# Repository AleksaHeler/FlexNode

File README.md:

# FlexNode

FlexNode is a DIY "smart home" system with a single hub and multiple flexible and customizable nodes.

## System Diagram

### Node proof of concept

Some images during building:

Grafana screenshots showing it in action:

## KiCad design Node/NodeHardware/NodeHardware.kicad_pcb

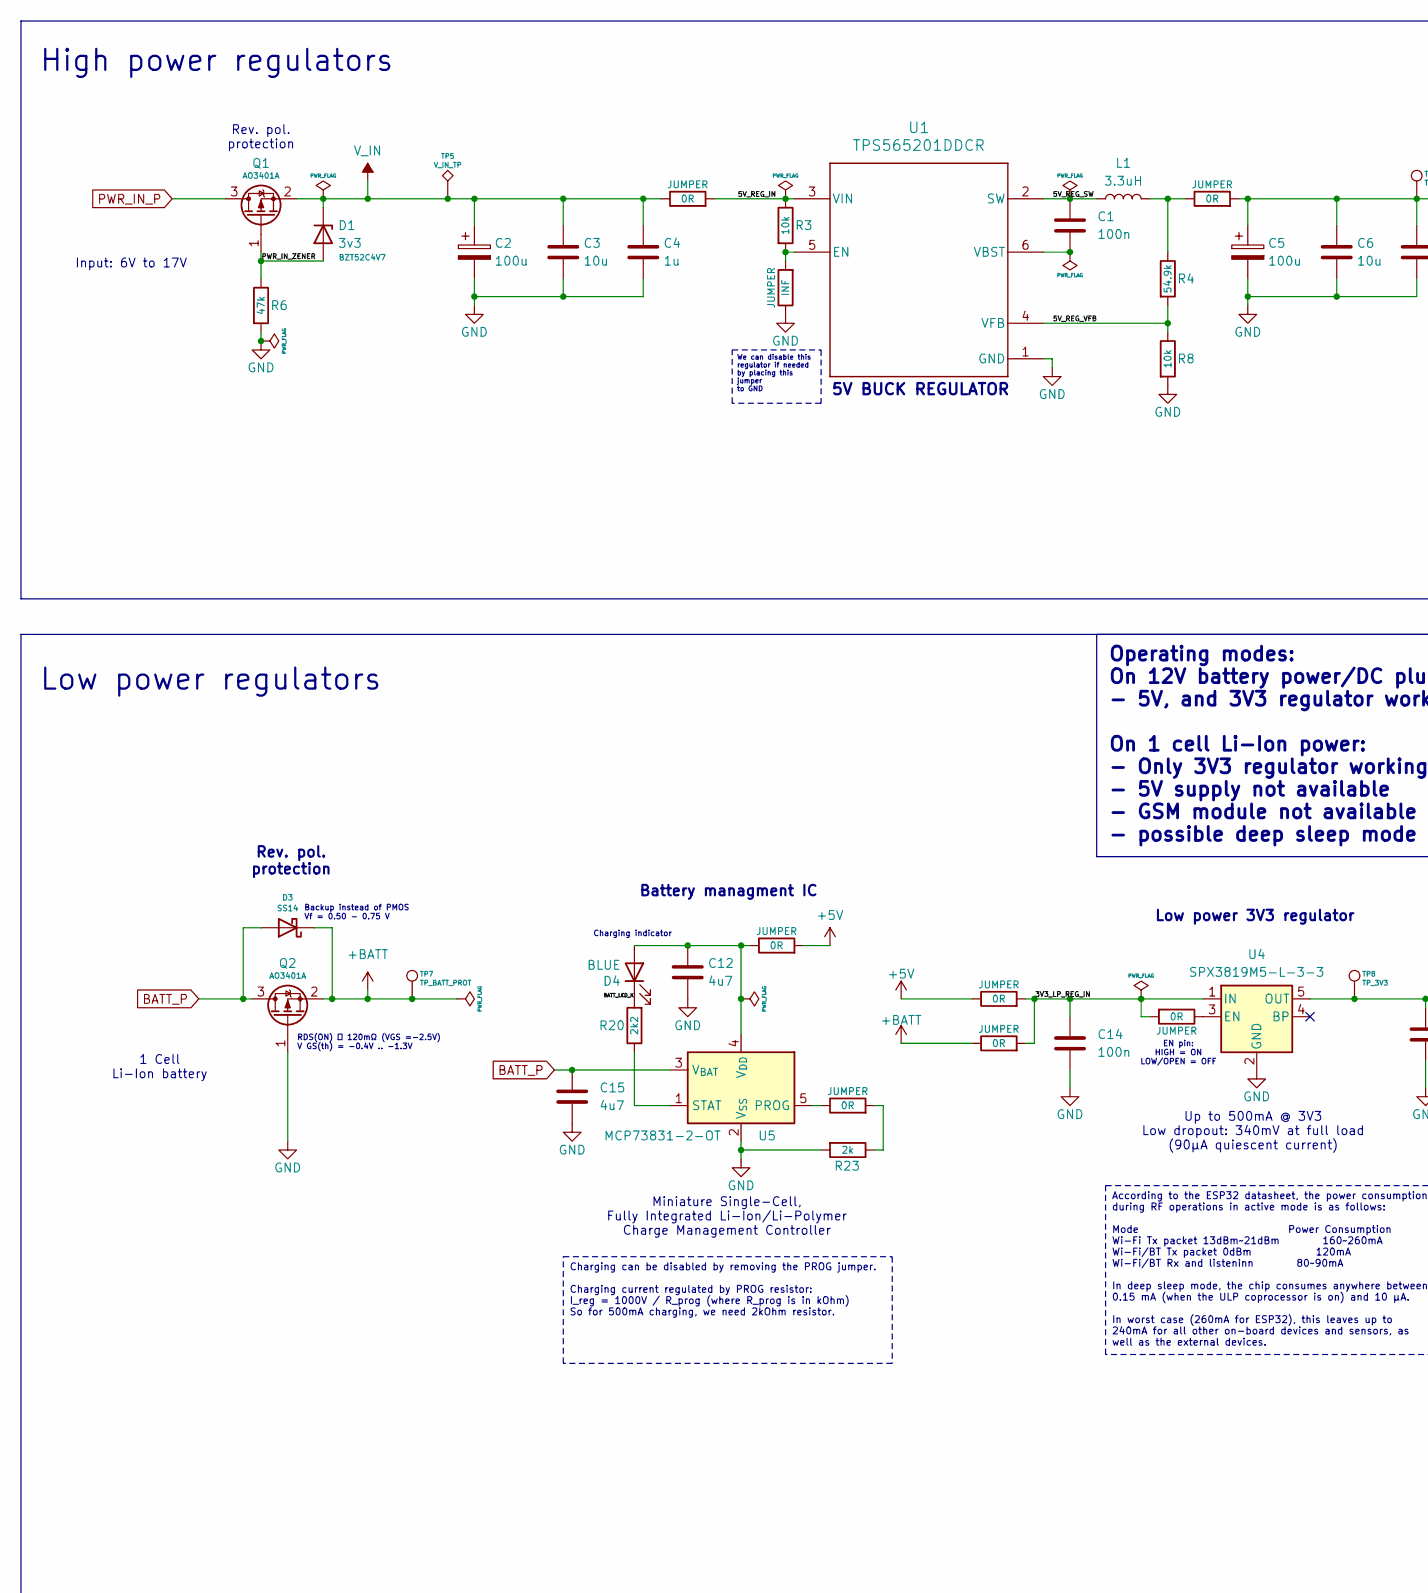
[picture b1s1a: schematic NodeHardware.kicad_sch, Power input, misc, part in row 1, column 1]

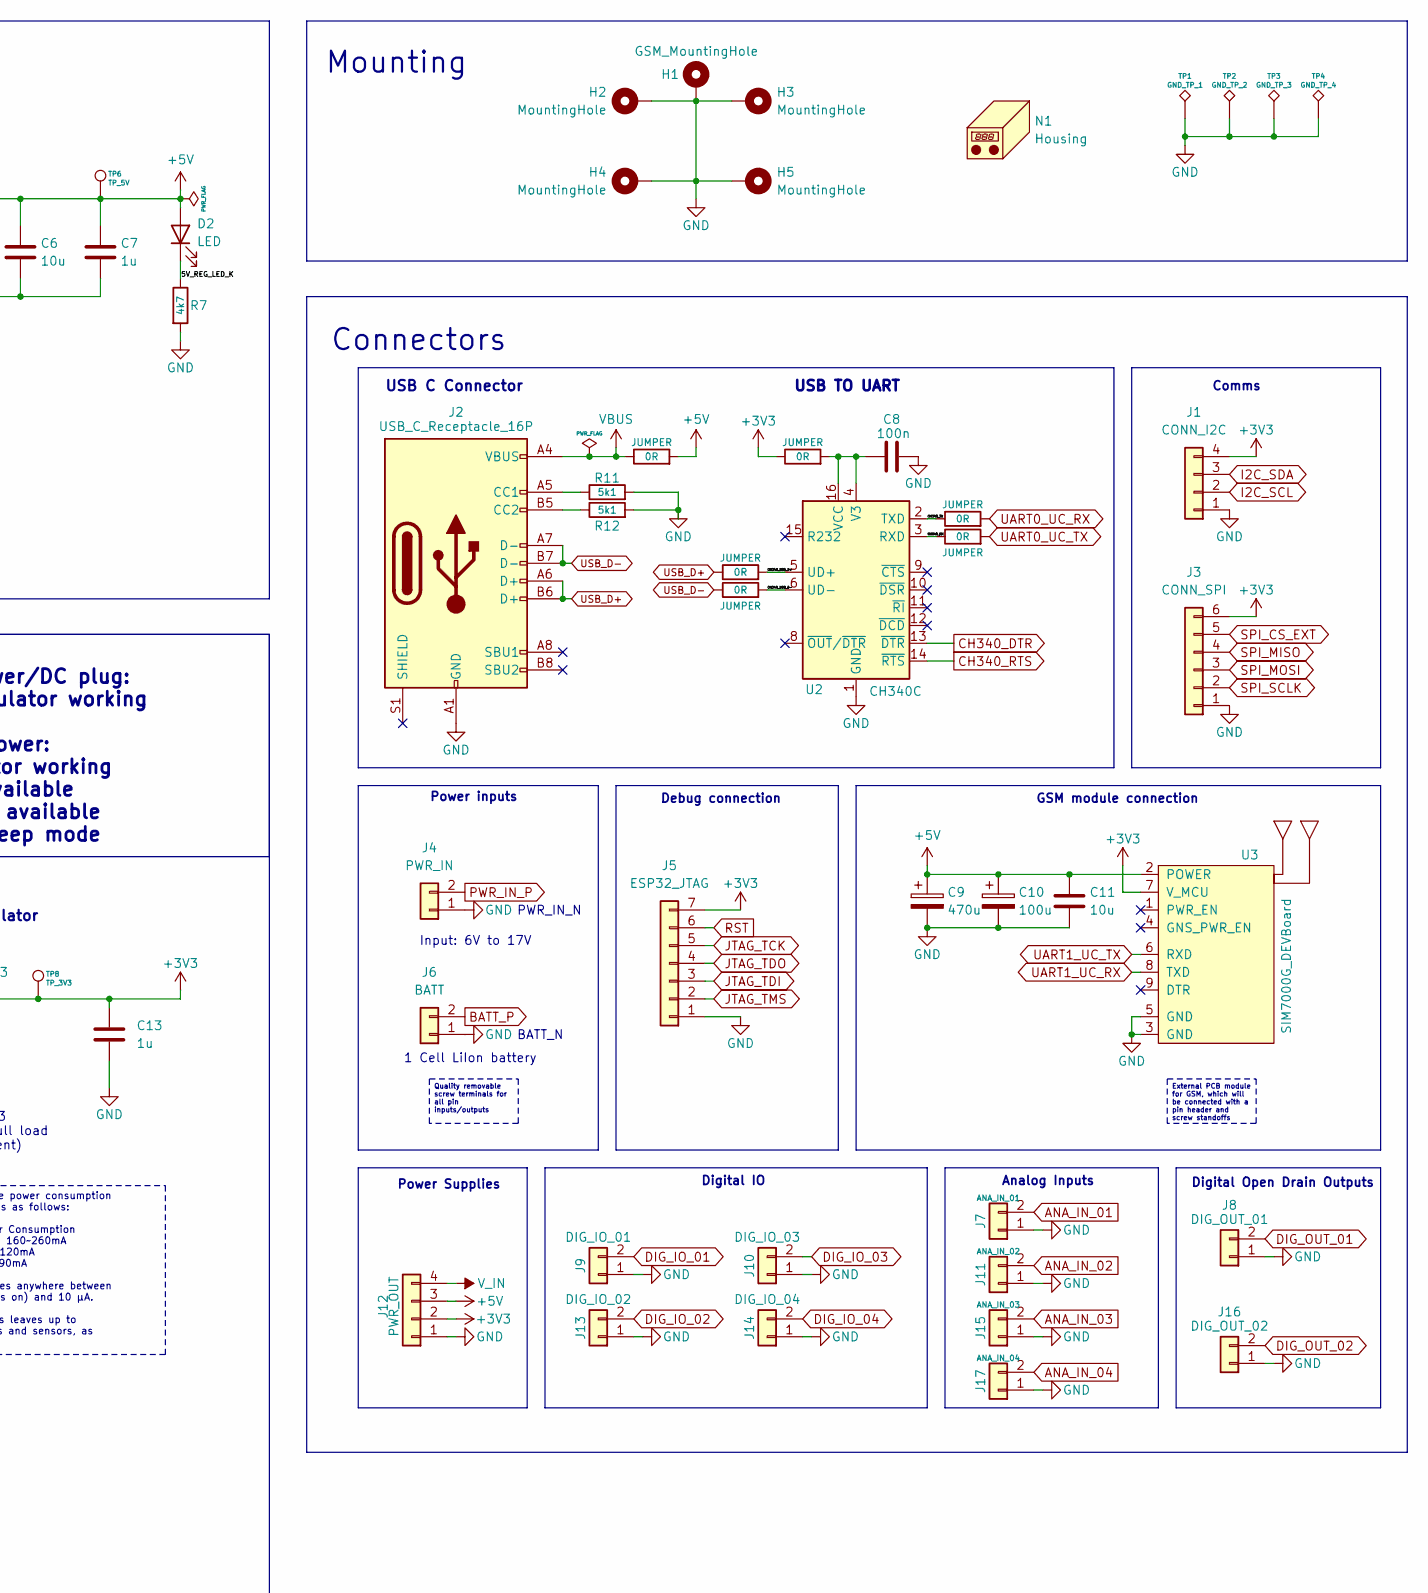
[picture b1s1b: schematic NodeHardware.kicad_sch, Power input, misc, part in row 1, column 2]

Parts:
C1, C8, C14: 100n; C_0805_2012Metric
C2, C5, C10: 100u; CP_Elec_6.3x7.7
C3, C6, C11: 10u; C_0805_2012Metric
C4, C7, C13: 1u; C_0805_2012Metric
C9: 470u; CP_Elec_6.3x7.7
C12, C15: 4u7; C_0805_2012Metric
D1: 3v3; D_SOD-123; Part Name BZT52C4V7
D2: LED; LED_1210_3225Metric
D3: SS14; D_SMA
D4: BLUE; LED_1210_3225Metric
H1: GSM_MountingHole; MountingHole_3.2mm_M3_Pad_Via
H2, H3, H4, H5: MountingHole; MountingHole_3.2mm_M3_Pad_Via
J1: CONN_I2C; TerminalBlock_bornier-4_P5.08mm
J2: USB_C_Receptacle_16P; USB_C_Receptacle_G-Switch_GT-USB-7010ASV
J3: CONN_SPI; TerminalBlock_bornier-6_P5.08mm
J4: PWR_IN; TerminalBlock_bornier-2_P5.08mm
J5: ESP32_JTAG; PinHeader_1x07_P2.54mm_Vertical
J6: BATT; TerminalBlock_bornier-2_P5.08mm
J7: ANA_IN_01; TerminalBlock_bornier-2_P5.08mm
J8: DIG_OUT_01; TerminalBlock_bornier-2_P5.08mm
J9: DIG_IO_01; TerminalBlock_bornier-2_P5.08mm
J10: DIG_IO_03; TerminalBlock_bornier-2_P5.08mm
J11: ANA_IN_02; TerminalBlock_bornier-2_P5.08mm
J12: PWR_OUT; TerminalBlock_bornier-4_P5.08mm
J13: DIG_IO_02; TerminalBlock_bornier-2_P5.08mm
J14: DIG_IO_04; TerminalBlock_bornier-2_P5.08mm
J15: ANA_IN_03; TerminalBlock_bornier-2_P5.08mm
J16: DIG_OUT_02; TerminalBlock_bornier-2_P5.08mm
J17: ANA_IN_04; TerminalBlock_bornier-2_P5.08mm
L1: 3.3uH; L_6.3x6.3_H3
N1: Housing; PlasticEnclosure_150x110x70
Q1, Q2: AO3401A; SOT-23
R1, R2, R9, R10, R13, R14, R15, R16, R17, R18, R19, R21, R22: 0R; R_0805_2012Metric
R3, R8: 10k; R_0805_2012Metric
R4: 54.9k; R_0805_2012Metric
R5: INF; R_0805_2012Metric
R6: 47k; R_0805_2012Metric
R7: 4k7; R_0805_2012Metric
R11, R12: 5k1; R_0805_2012Metric
R20: 2k2; R_0805_2012Metric
R23: 2k; R_0805_2012Metric
TP1: GND_TP_1; TestPoint_Pad_D2.0mm
TP2: GND_TP_2; TestPoint_Pad_D2.0mm
TP3: GND_TP_3; TestPoint_Pad_D2.0mm
TP4: GND_TP_4; TestPoint_Pad_D2.0mm
TP5: V_IN_TP; TestPoint_Pad_D2.0mm
TP6: TP_5V; TestPoint_Pad_D2.0mm
TP7: TP_BATT_PROT; TestPoint_Pad_D2.0mm
TP8: TP_3V3; TestPoint_Pad_D2.0mm
U1: TPS565201DDCR; TPS565201DDCR_L
U2: CH340C; SOIC-16_3.9x9.9mm_P1.27mm
U3: SIM7000G_DEVBoard; sim7000G_dev_board_rev3
U4: SPX3819M5-L-3-3; SOT-23-5
U5: MCP73831-2-OT; SOT-23-5

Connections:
+3V3: C13.1, J1.4, J3.6, J5.7, J12.2, R10.1, TP8.1, U3.7 (V_MCU), U4.5 (OUT); also elsewhere on the board
+5V: C5.1, C6.1, C7.1, C9.1, C10.1, C11.1, D2.2 (A), J12.3, R2.2, R9.2, R17.2, R18.1, TP6.1, U3.2 (POWER); also elsewhere on the board
+BATT: D3.1 (K), Q2.2 (S), R21.1, TP7.1; also elsewhere on the board
/3V3_LP_REG_IN: C14.1, R18.2, R19.2, R21.2, U4.1 (IN)
/5V_REG_IN: R1.2, R3.1, U1.3 (VIN)
/5V_REG_LED_K: D2.1 (K), R7.1
/5V_REG_SW: C1.1, L1.1, U1.2 (SW)
/5V_REG_VFB: R4.2, R8.1, U1.4 (VFB)
/BATT_LED_K: D4.1 (K), R20.2
/CH340_RX: R14.1, U2.3 (RXD)
/CH340_TX: R13.1, U2.2 (TXD)
/CH340_USB_D+: R15.2, U2.5 (UD+)
/CH340_USB_D-: R16.2, U2.6 (UD-)
/PWR_IN_ZENER: D1.2 (A), Q1.1 (G), R6.1
ANA_IN_01: J7.2; also elsewhere on the board
ANA_IN_02: J11.2; also elsewhere on the board
ANA_IN_03: J15.2; also elsewhere on the board
ANA_IN_04: J17.2; also elsewhere on the board
BATT_P: C15.1, D3.2 (A), J6.2, Q2.3 (D), U5.3 (V_{BAT})
CH340_DTR: U2.13 (~DTR); also elsewhere on the board
CH340_RTS: U2.14 (~RTS); also elsewhere on the board
DIG_IO_01: J9.2; also elsewhere on the board
DIG_IO_02: J13.2; also elsewhere on the board
DIG_IO_03: J10.2; also elsewhere on the board
DIG_IO_04: J14.2; also elsewhere on the board
DIG_OUT_01: J8.2; also elsewhere on the board
DIG_OUT_02: J16.2; also elsewhere on the board
GND: C2.2, C3.2, C4.2, C5.2, C6.2, C7.2, C8.2, C9.2, C10.2, C11.2, C12.2, C13.2, C14.2, C15.2, H1.1, H2.1, H3.1, H4.1, H5.1, J1.1, J2.A1 (GND), J2.A12 (GND), J2.B1 (GND), J2.B12 (GND), J3.1, J4.1, J5.1, J6.1, J7.1, J8.1, J9.1, J10.1, J11.1, J12.1, J13.1, J14.1, J15.1, J16.1, J17.1, Q2.1 (G), R5.1, R6.2, R7.2, R8.2, R11.2, R12.2, R23.2, TP1.1, TP2.1, TP3.1, TP4.1, U1.1 (GND), U2.1 (GND), U3.3 (GND), U3.5 (GND), U4.2 (GND), U5.2 (V_{SS}); also elsewhere on the board
I2C_SCL: J1.2; also elsewhere on the board
I2C_SDA: J1.3; also elsewhere on the board
JTAG_TCK: J5.5; also elsewhere on the board
JTAG_TDI: J5.3; also elsewhere on the board
JTAG_TDO: J5.4; also elsewhere on the board
JTAG_TMS: J5.2; also elsewhere on the board
unnamed: C12.1, D4.2 (A), R17.1, U5.4 (V_{DD})
unnamed: J2.A5 (CC1), R11.1
unnamed: J2.B5 (CC2), R12.1
unnamed: L1.2, R2.1, R4.1
unnamed: R22.2, R23.1
unnamed: R3.2, R5.2, U1.5 (EN)
unnamed: C1.2, U1.6 (VBST)
unnamed: C8.1, R10.2, U2.4 (V3), U2.16 (VCC)
unnamed: R19.1, U4.3 (EN)
unnamed: R22.1, U5.5 (PROG)
unnamed: R20.1, U5.1 (STAT)
PWR_IN_P: J4.2, Q1.3 (D)
RST: J5.6; also elsewhere on the board
SPI_CS_EXT: J3.5; also elsewhere on the board
SPI_MISO: J3.4; also elsewhere on the board
SPI_MOSI: J3.3; also elsewhere on the board
SPI_SCLK: J3.2; also elsewhere on the board
UART0_UC_RX: R13.2; also elsewhere on the board
UART0_UC_TX: R14.2; also elsewhere on the board
UART1_UC_RX: U3.8 (TXD); also elsewhere on the board
UART1_UC_TX: U3.6 (RXD); also elsewhere on the board
USB_D+: J2.A6 (D+), J2.B6 (D+), R15.1; also elsewhere on the board
USB_D-: J2.A7 (D-), J2.B7 (D-), R16.1; also elsewhere on the board
VBUS: J2.A4 (VBUS), J2.A9 (VBUS), J2.B4 (VBUS), J2.B9 (VBUS), R9.1
V_IN: C2.1, C3.1, C4.1, D1.1 (K), J12.4, Q1.2 (S), R1.1, TP5.1; also elsewhere on the board

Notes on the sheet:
We can disable this regulator if needed by placing this jumper to GND
External PCB module for GSM, which will be connected with a pin header and screw standoffs
Quality removable screw terminals for all pin inputs/outputs
Charging can be disabled by removing the PROG jumper. Charging current regulated by PROG resistor: I_reg = 1000V / R_prog (where R_prog is in kOhm) So for 500mA charging, we need 2kOhm resistor.
Operating modes: On 12V battery power/DC plug: - 5V, and 3V3 regulator working On 1 cell Li-Ion power: - Only 3V3 regulator working - 5V supply not available - GSM module not available - possible deep sleep mode
According to the ESP32 datasheet, the power consumption during RF operations in active mode is as follows: Mode Power Consumption Wi-Fi Tx packet 13dBm~21dBm 160~260mA Wi-Fi/BT Tx packet 0dBm 120mA Wi-Fi/BT Rx and listeninn 80~90mA In deep sleep mode, the chip consumes anywhere between 0.15 mA (whe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
Battery managment IC
1 Cell Li-Ion battery
Power Supplies
Charging indicator
Connectors
Low power 3V3 regulator
PWR_IN_N
Debug connection
Input: 6V to 17V
Power inputs
USB TO UART
Rev. pol. protection
Analog Inputs
Backup instead of PMOS Vf = 0.50 - 0.75 V
Comms
5V BUCK REGULATOR
EN pin: HIGH = ON LOW/OPEN = OFF
USB C Connector
RDS(ON) ＜ 120mΩ (VGS =-2.5V) V GS(th) = -0.4V .. -1.3V
GSM module connection
Low power regulators
Digital IO
1 Cell LiIon battery
BATT_N
Mounting
Digital Open Drain Outputs
High power regulators
Up to 500mA @ 3V3 Low dropout: 340mV at full load (90μA quiescent current)
Miniature Single-Cell, Fully Integrated Li-Ion/Li-Polymer Charge Management Controller
